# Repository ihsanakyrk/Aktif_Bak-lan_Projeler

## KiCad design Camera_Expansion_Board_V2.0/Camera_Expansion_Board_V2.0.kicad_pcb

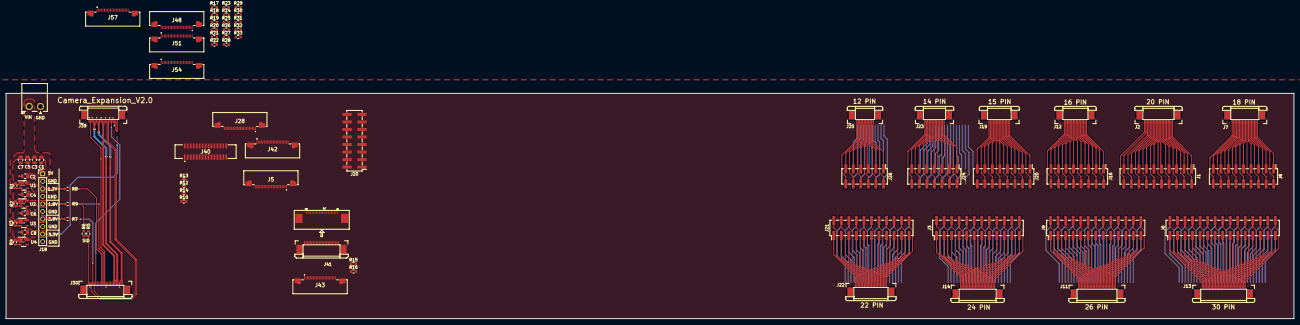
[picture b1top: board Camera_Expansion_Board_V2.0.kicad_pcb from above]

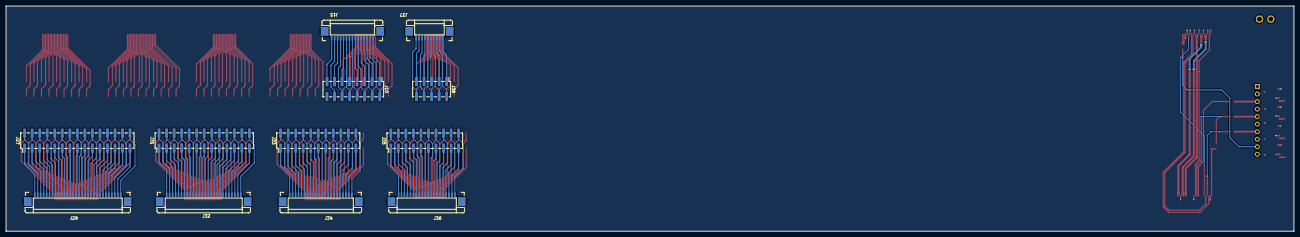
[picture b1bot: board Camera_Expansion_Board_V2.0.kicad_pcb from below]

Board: 2 copper layers, 434.4 x 76.0 mm, 92 parts (12 on the bottom side), 377 nets.

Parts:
C1, C2, C3, C4, C5, C6, C7, C8: 10uF; C_0805_2012Metric
J1, J35: PinHeader_2x10_P2.54mm_Vertical_MALE_SMD; PinHeader_2x10_P2.54mm_Vertical_SMD
J2, J39: FPC-05F-20PH20; FFC SOCKET DR_DWN 0.5MM -20P
J3: PinHeader_2x12_P2.54mm_Vertical_MALE_SMD; PinHeader_2x12_P2.54mm_Vertical_SMD
J4: 52435-2271
J5, J28, J42, J43, J48, J51, J54, J57: FFC SOCKET DR_BOTTOM 0.5MM -22P; F32R1A7H111022
J6, J27: PinHeader_2x15_P2.54mm_Vertical_MALE_SMD; PinHeader_2x15_P2.54mm_Vertical_SMD
J7: FPC-05F-18PH20; FFC SOCKET DR_DWN 0.5MM -18P
J8: PinHeader_2x9_P2.54mm_Vertical_MALE_SMD; PinHeader_2x09_P2.54mm_Vertical_SMD
J9, J31: PinHeader_2x13_P2.54mm_Vertical_MALE_SMD; PinHeader_2x13_P2.54mm_Vertical_SMD
J10: PinHeader_2x08_P2.54mm_Vertical_MALE_SMD; PinHeader_2x08_P2.54mm_Vertical_SMD
J11: FPC-05F-26PH20; FFC SOCKET DR_DWN 0.5MM-26P
J12: FPC-05F-16PH20; FFC SOCKET DR_DWN 0.5MM -16P
J13: FPC-05F-30PH20; FFC SOCKET DR_DWN 0.5MM-30P
J14, J30, J41: FPC-05F-24PH20; FFC SOCKET DR_DWN 0.5MM-24P
J15: AFA07-S15ECA-00
J16, J20, J20#2: PinHeader_2x8_P2.54mm_Vertical_MALE_SMD; PinHeader_2x08_P2.54mm_Vertical_SMD
J17: KF2EDGH-3.81-2P- Right Angle; KF2EDGH-3.81-2P
J18: PinHeader_1x10_P2.54mm_Vertical_MALE_TH; PinHeader_1x10_P2.54mm_Vertical
J19: FPC-05F-15PH20; FFC SOCKET DR_DWN 0.5MM -15P
J21, J33: PinHeader_2x11_P2.54mm_Vertical_MALE_SMD; PinHeader_2x11_P2.54mm_Vertical_SMD
J22: FPC-05F-22PH20; FFC SOCKET DR_DWN 0.5MM -22P
J23: FPC-05F-14PH20; FFC SOCKET DR_DWN 0.5MM -14P
J24: PinHeader_2x7_P2.54mm_Vertical_MALE_SMD; PinHeader_2x07_P2.54mm_Vertical_SMD
J25: FPC-05F-12PH20; FFC SOCKET DR_DWN 0.5MM -12P
J26: PinHeader_2x6_P2.54mm_Vertical_MALE_SMD; PinHeader_2x06_P2.54mm_Vertical_SMD
J29: AFA07-S30ECA-00
J32: AFA07-S26ECA-00
J34: AFA07-S22ECA-00
J36: AFA07-S20ECA-00
J37: AFA07-S10ECA-00
J38: PinHeader_2x5_P2.54mm_Vertical_MALE_SMD; PinHeader_2x05_P2.54mm_Vertical_SMD
J40: 117342485
R1, R2, R3, R4: 5K; R_0603_1608Metric
R5, R7, R8, R9, R15, R16, R17, R18, R19, R20, R21, R22, R23, R24, R25, R26, R27, R28, R29, R30, R31, R32, R33: 0R; R_0603_1608Metric
R6, R10: DNP; R_0603_1608Metric
R12, R13, R14: 0R; R_0402_1005Metric
U1: RT9080-12GJ5; SOT-23-5
U2: RT9080-18GJ5; SOT-23-5
U3: RT9080-28GJ5; SOT-23-5
U4: RT9080-33GJ5; SOT-23-5

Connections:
3V3: R12.1, R13.1, R14.1
/+3V3: J4.22, J39.19, J39.20, R10.2
/CSI2_CLK_N: J5.8, J28.15
/CSI2_CLK_P: J5.9, J28.14
/CSI2_D0_N: J5.2, J28.21
/CSI2_D0_P: J5.3, J28.20
/CSI2_D1_N: J5.5, J28.18
/CSI2_D1_P: J5.6, J28.17
/CSI_C_N: J42.15, J43.15, J48.15, J51.15, J54.15, J57.15
/CSI_C_P: J42.14, J43.14, J48.14, J51.14, J54.14, J57.14
/CSI_D0_N: J42.21, J43.21, J48.21, J51.21, J54.21, J57.21
/CSI_D0_P: J42.20, J43.20, J48.20, J51.20, J54.20, J57.20
/CSI_D1_N: J42.18, J43.18, J48.18, J51.18, J54.18, J57.18
/CSI_D1_P: J42.17, J43.17, J48.17, J51.17, J54.17, J57.17
/CSI_D2_N: J42.12, J43.12, J48.12, J51.12, J54.12, J57.12
/CSI_D2_P: J42.11, J43.11, J48.11, J51.11, J54.11, J57.11
/CSI_D3_N: J42.9, J43.9, J48.9, J51.9, J54.9, J57.9
/CSI_D3_P: J42.8, J43.8, J48.8, J51.8, J54.8, J57.8
/EXT_XVCLK: J5.17, J28.6, J42.6, J43.6, J48.6, J51.6, J54.6, J57.6
/FSIN: J5.18, J28.5, J42.5, J43.5, J48.5, J51.5, J54.5, J57.5
/I2C_SCL: J42.3, J43.3, J48.3, J51.3, J54.3, J57.3
/I2C_SDA: J42.2, J43.2, J48.2, J51.2, J54.2, J57.2
/MCLK: J30.12, J39.2
/MCN: J30.24, J39.8
/MCP: J30.23, J39.7
/MDN0: J30.21, J39.5
/MDN1: J30.19, J39.11
/MDP0: J30.20, J39.4
/MDP1: J30.18, J39.10
/MIPI_I2C_SCL: J5.20, J28.3, J30.5, J39.13
/MIPI_I2C_SDA: J5.21, J28.2, J30.3, J39.14
/MIPI_LVDS_RST: J30.6, J39.16
/SID: J30.1, R5.2, R6.1
AVDD: J30.4, R7.1
DGND: J5.1, J5.4, J5.7, J5.10, J5.13, J5.16, J5.19, J28.4, J28.7, J28.10, J28.13, J28.16, J28.19, J28.22
DOVDD: J30.11, R6.2, R9.1
DVDD: J30.10, R8.1
GND: C1.2, C2.2, C3.2, C4.2, C5.2, C6.2, C7.2, C8.2, J2.21, J2.22, J4.1, J4.4, J4.7, J4.10, J4.13, J4.16, J4.19, J5.23, J5.24, J7.19, J7.20, J11.27, J11.28, J12.17, J12.18, J13.31 (Pin_29), J13.32 (Pin_30), J14.25 (Pin_23), J14.26 (Pin_24), J15.16 (Pin_14), J15.17 (Pin_15), J17.1, J18.2, J18.4, J18.6, J18.8, J18.10, J19.16, J19.17, J22.23, J22.24, J23.15, J23.16, J25.13, J25.14, J28.23, J28.24, J29.31 (Pin_29), J29.32 (Pin_30), J30.2, J30.13, J30.22, J30.25 (Pin_23), J30.26 (Pin_24), J32.27, J32.28, J34.23, J34.24, J36.21, J36.22, J37.11, J37.12, J39.1, J39.3, J39.6, J39.9, J39.12, J39.15, J39.17, J39.18, J39.21, J39.22, J40.1, J40.7, J40.13, J40.19, J41.1, J41.2, J41.11, J42.4, J42.7, J42.10, J42.13, J42.16, J42.19, J42.22, J42.23, J42.24, J43.4, J43.7, J43.10, J43.13, J43.16, J43.19, J43.22, J43.23, J43.24, J48.4, J48.7, J48.10, J48.13, J48.16, J48.19, J48.22, J48.23, J48.24, J51.4, J51.7, J51.10, J51.13, J51.16, J51.19, J51.22, J51.23, J51.24, J54.4, J54.7, J54.10, J54.13, J54.16, J54.19, J54.22, J54.23, J54.24, J57.4, J57.7, J57.10, J57.13, J57.16, J57.19, J57.22, J57.23, J57.24, R5.1, U1.2 (GND), U2.2 (GND), U3.2 (GND), U4.2 (GND)
unnamed: J1.1, J2.1
unnamed: J1.2, J2.2
unnamed: J1.3, J2.3
unnamed: J1.4, J2.4
unnamed: J1.5, J2.5
unnamed: J1.6, J2.6
unnamed: J1.7, J2.7
unnamed: J1.8, J2.8
unnamed: J1.9, J2.9
unnamed: J1.10, J2.10
unnamed: J1.11, J2.11
unnamed: J1.12, J2.12
unnamed: J1.13, J2.13
unnamed: J1.14, J2.14
unnamed: J1.15, J2.15
unnamed: J1.16, J2.16
unnamed: J1.17, J2.17
unnamed: J1.18, J2.18
unnamed: J1.19, J2.19
unnamed: J1.20, J2.20
unnamed: J3.23, J14.23
unnamed: J3.24, J14.24
unnamed: J5.22, R12.2
unnamed: J6.29, J13.29
unnamed: J6.30, J13.30
unnamed: J7.1, J8.1
unnamed: J7.2, J8.2
unnamed: J7.3, J8.3
unnamed: J7.4, J8.4
unnamed: J7.5, J8.5
unnamed: J7.6, J8.6
unnamed: J7.7, J8.7
unnamed: J7.8, J8.8
unnamed: J7.9, J8.9
unnamed: J7.10, J8.10
unnamed: J7.11, J8.11
unnamed: J7.12, J8.12
unnamed: J7.13, J8.13
unnamed: J7.14, J8.14
unnamed: J7.15, J8.15
unnamed: J7.16, J8.16
unnamed: J7.17, J8.17
unnamed: J7.18, J8.18
unnamed: J10.1, J15.1
unnamed: J10.2, J15.2
unnamed: J10.3, J15.3
unnamed: J10.4, J15.4
unnamed: J10.5, J15.5
unnamed: J10.6, J15.6
unnamed: J10.7, J15.7
unnamed: J10.8, J15.8
unnamed: J10.9, J15.9
unnamed: J10.10, J15.10
unnamed: J10.11, J15.11
unnamed: J10.12, J15.12
unnamed: J10.13, J15.13
unnamed: J10.14, J15.14
unnamed: J10.15, J15.15
unnamed: J9.1, J11.1
unnamed: J9.2, J11.2
unnamed: J9.3, J11.3
unnamed: J9.4, J11.4
unnamed: J9.5, J11.5
unnamed: J9.6, J11.6
unnamed: J9.7, J11.7
unnamed: J9.8, J11.8
unnamed: J9.9, J11.9
unnamed: J9.10, J11.10
unnamed: J9.11, J11.11
unnamed: J9.12, J11.12
unnamed: J9.13, J11.13
unnamed: J9.14, J11.14
unnamed: J9.15, J11.15
unnamed: J9.16, J11.16
unnamed: J9.17, J11.17
unnamed: J9.18, J11.18
unnamed: J9.19, J11.19
unnamed: J9.20, J11.20
unnamed: J9.21, J11.21
unnamed: J9.22, J11.22
unnamed: J9.23, J11.23
unnamed: J9.24, J11.24
unnamed: J9.25, J11.25
unnamed: J9.26, J11.26
unnamed: J12.1, J16.1
unnamed: J12.2, J16.2
unnamed: J12.3, J16.3
unnamed: J12.4, J16.4
unnamed: J12.5, J16.5
unnamed: J12.6, J16.6
unnamed: J12.7, J16.7
unnamed: J12.8, J16.8
unnamed: J12.9, J16.9
unnamed: J12.10, J16.10
unnamed: J12.11, J16.11
unnamed: J12.12, J16.12
unnamed: J12.13, J16.13
unnamed: J12.14, J16.14
unnamed: J12.15, J16.15
unnamed: J12.16, J16.16
unnamed: J6.1, J13.1
unnamed: J6.2, J13.2
unnamed: J6.3, J13.3
unnamed: J6.4, J13.4
unnamed: J6.5, J13.5
unnamed: J6.6, J13.6
unnamed: J6.7, J13.7
unnamed: J6.8, J13.8
unnamed: J6.9, J13.9
unnamed: J6.10, J13.10
unnamed: J6.11, J13.11
unnamed: J6.12, J13.12
unnamed: J6.13, J13.13
unnamed: J6.14, J13.14
unnamed: J6.15, J13.15
unnamed: J6.16, J13.16
unnamed: J6.17, J13.17
unnamed: J6.18, J13.18
unnamed: J6.19, J13.19
unnamed: J6.20, J13.20
unnamed: J6.21, J13.21
unnamed: J6.22, J13.22
unnamed: J6.23, J13.23
unnamed: J6.24, J13.24
unnamed: J6.25, J13.25
unnamed: J6.26, J13.26
unnamed: J6.27, J13.27
unnamed: J6.28, J13.28
unnamed: J3.1, J14.1
unnamed: J3.2, J14.2
unnamed: J3.3, J14.3
unnamed: J3.4, J14.4
unnamed: J3.5, J14.5
unnamed: J3.6, J14.6
unnamed: J3.7, J14.7
unnamed: J3.8, J14.8
unnamed: J3.9, J14.9
unnamed: J3.10, J14.10
unnamed: J3.11, J14.11
unnamed: J3.12, J14.12
unnamed: J3.13, J14.13
unnamed: J3.14, J14.14
unnamed: J3.15, J14.15
unnamed: J3.16, J14.16
unnamed: J3.17, J14.17
unnamed: J3.18, J14.18
unnamed: J3.19, J14.19
unnamed: J3.20, J14.20
unnamed: J3.21, J14.21
unnamed: J3.22, J14.22
unnamed: J19.1, J20.1, J20#2.1
unnamed: J19.2, J20.2, J20#2.2
unnamed: J19.3, J20.3, J20#2.3
unnamed: J19.4, J20.4, J20#2.4
unnamed: J19.5, J20.5, J20#2.5
unnamed: J19.6, J20.6, J20#2.6
unnamed: J19.7, J20.7, J20#2.7
unnamed: J19.8, J20.8, J20#2.8
unnamed: J19.9, J20.9, J20#2.9
unnamed: J19.10, J20.10, J20#2.10
unnamed: J19.11, J20.11, J20#2.11
unnamed: J19.12, J20.12, J20#2.12
unnamed: J19.13, J20.13, J20#2.13
unnamed: J19.14, J20.14, J20#2.14
unnamed: J19.15, J20.15, J20#2.15
unnamed: J21.1, J22.1
unnamed: J21.2, J22.2
unnamed: J21.3, J22.3
unnamed: J21.4, J22.4
unnamed: J21.5, J22.5
unnamed: J21.6, J22.6
unnamed: J21.7, J22.7
unnamed: J21.8, J22.8
unnamed: J21.9, J22.9
unnamed: J21.10, J22.10
unnamed: J21.11, J22.11
unnamed: J21.12, J22.12
unnamed: J21.13, J22.13
unnamed: J21.14, J22.14
unnamed: J21.15, J22.15
unnamed: J21.16, J22.16
unnamed: J21.17, J22.17
unnamed: J21.18, J22.18
unnamed: J21.19, J22.19
unnamed: J21.20, J22.20
unnamed: J21.21, J22.21
unnamed: J21.22, J22.22
unnamed: J23.1, J24.1
unnamed: J23.2, J24.2
unnamed: J23.3, J24.3
unnamed: J23.4, J24.4
unnamed: J23.5, J24.5
unnamed: J23.6, J24.6
unnamed: J23.7, J24.7
unnamed: J23.8, J24.8
unnamed: J23.9, J24.9
unnamed: J23.10, J24.10
unnamed: J23.11, J24.11
unnamed: J23.12, J24.12
unnamed: J23.13, J24.13
unnamed: J23.14, J24.14
unnamed: J25.1, J26.1
unnamed: J25.2, J26.2
unnamed: J25.3, J26.3
unnamed: J25.4, J26.4
unnamed: J25.5, J26.5
unnamed: J25.6, J26.6
unnamed: J25.7, J26.7
unnamed: J25.8, J26.8
unnamed: J25.9, J26.9
unnamed: J25.10, J26.10
unnamed: J25.11, J26.11
unnamed: J25.12, J26.12
unnamed: J27.1, J29.1
unnamed: J27.2, J29.2
unnamed: J27.3, J29.3
unnamed: J27.4, J29.4
unnamed: J27.5, J29.5
unnamed: J27.6, J29.6
unnamed: J27.7, J29.7
unnamed: J27.8, J29.8
unnamed: J27.9, J29.9
unnamed: J27.10, J29.10
unnamed: J27.11, J29.11
unnamed: J27.12, J29.12
unnamed: J27.13, J29.13
unnamed: J27.14, J29.14
unnamed: J27.15, J29.15
unnamed: J27.16, J29.16
unnamed: J27.17, J29.17
unnamed: J27.18, J29.18
unnamed: J27.19, J29.19
unnamed: J27.20, J29.20
unnamed: J27.21, J29.21
unnamed: J27.22, J29.22
unnamed: J27.23, J29.23
unnamed: J27.24, J29.24
unnamed: J27.25, J29.25
unnamed: J27.26, J29.26
unnamed: J27.27, J29.27
unnamed: J27.28, J29.28
unnamed: J27.29, J29.29
unnamed: J27.30, J29.30
unnamed: J28.1, R13.2
unnamed: J31.1, J32.1
unnamed: J31.2, J32.2
unnamed: J31.3, J32.3
unnamed: J31.4, J32.4
unnamed: J31.5, J32.5
unnamed: J31.6, J32.6
unnamed: J31.7, J32.7
unnamed: J31.8, J32.8
unnamed: J31.9, J32.9
unnamed: J31.10, J32.10
unnamed: J31.11, J32.11
unnamed: J31.12, J32.12
unnamed: J31.13, J32.13
unnamed: J31.14, J32.14
unnamed: J31.15, J32.15
unnamed: J31.16, J32.16
unnamed: J31.17, J32.17
unnamed: J31.18, J32.18
unnamed: J31.19, J32.19
unnamed: J31.20, J32.20
unnamed: J31.21, J32.21
unnamed: J31.22, J32.22
unnamed: J31.23, J32.23
unnamed: J31.24, J32.24
unnamed: J31.25, J32.25
unnamed: J31.26, J32.26
unnamed: J33.1, J34.1
unnamed: J33.2, J34.2
unnamed: J33.3, J34.3
unnamed: J33.4, J34.4
unnamed: J33.5, J34.5
unnamed: J33.6, J34.6
unnamed: J33.7, J34.7
unnamed: J33.8, J34.8
unnamed: J33.9, J34.9
unnamed: J33.10, J34.10
unnamed: J33.11, J34.11
unnamed: J33.12, J34.12
unnamed: J33.13, J34.13
unnamed: J33.14, J34.14
unnamed: J33.15, J34.15
unnamed: J33.16, J34.16
unnamed: J33.17, J34.17
unnamed: J33.18, J34.18
unnamed: J33.19, J34.19
unnamed: J33.20, J34.20
unnamed: J33.21, J34.21
unnamed: J33.22, J34.22
unnamed: J35.1, J36.1
unnamed: J35.2, J36.2
unnamed: J35.3, J36.3
unnamed: J35.4, J36.4
unnamed: J35.5, J36.5
unnamed: J35.6, J36.6
unnamed: J35.7, J36.7
unnamed: J35.8, J36.8
unnamed: J35.9, J36.9
unnamed: J35.10, J36.10
unnamed: J35.11, J36.11
unnamed: J35.12, J36.12
unnamed: J35.13, J36.13
unnamed: J35.14, J36.14
unnamed: J35.15, J36.15
unnamed: J35.16, J36.16
unnamed: J35.17, J36.17
unnamed: J35.18, J36.18
unnamed: J35.19, J36.19
unnamed: J35.20, J36.20
unnamed: J37.1, J38.1
unnamed: J37.2, J38.2
unnamed: J37.3, J38.3
unnamed: J37.4, J38.4
unnamed: J37.5, J38.5
unnamed: J37.6, J38.6
unnamed: J37.7, J38.7
unnamed: J37.8, J38.8
unnamed: J37.9, J38.9
unnamed: J37.10, J38.10
unnamed: J42.1, R15.2
unnamed: J43.1, R16.2
unnamed: J48.1, R21.2
unnamed: J51.1, R24.2
unnamed: J54.1, R27.2
unnamed: J57.1, R30.2
unnamed: R1.2, U1.3 (EN)
unnamed: R2.2, U2.3 (EN)
unnamed: R3.2, U3.3 (EN)
unnamed: R4.2, U4.3 (EN)
VCC: R17.1, R18.1, R19.1, R20.1, R22.1, R23.1, R25.1, R26.1, R28.1, R29.1, R31.1, R32.1
VCC_3V3: C8.1, J18.9, R10.1, U4.5 (OUT)
VDD_3V3: R15.1, R16.1, R21.1, R24.1, R27.1, R30.1, R33.1
VIN: C1.1, C3.1, C5.1, C7.1, J17.2, J18.1, R1.1, R2.1, R3.1, R4.1, U1.1 (IN), U2.1 (IN), U3.1 (IN), U4.1 (IN)
VOUT_1.2: C2.1, J18.3, R8.2, U1.5 (OUT)
VOUT_1.8: C4.1, J18.5, R9.2, U2.5 (OUT)
VOUT_2.8: C6.1, J18.7, R7.2, U3.5 (OUT)

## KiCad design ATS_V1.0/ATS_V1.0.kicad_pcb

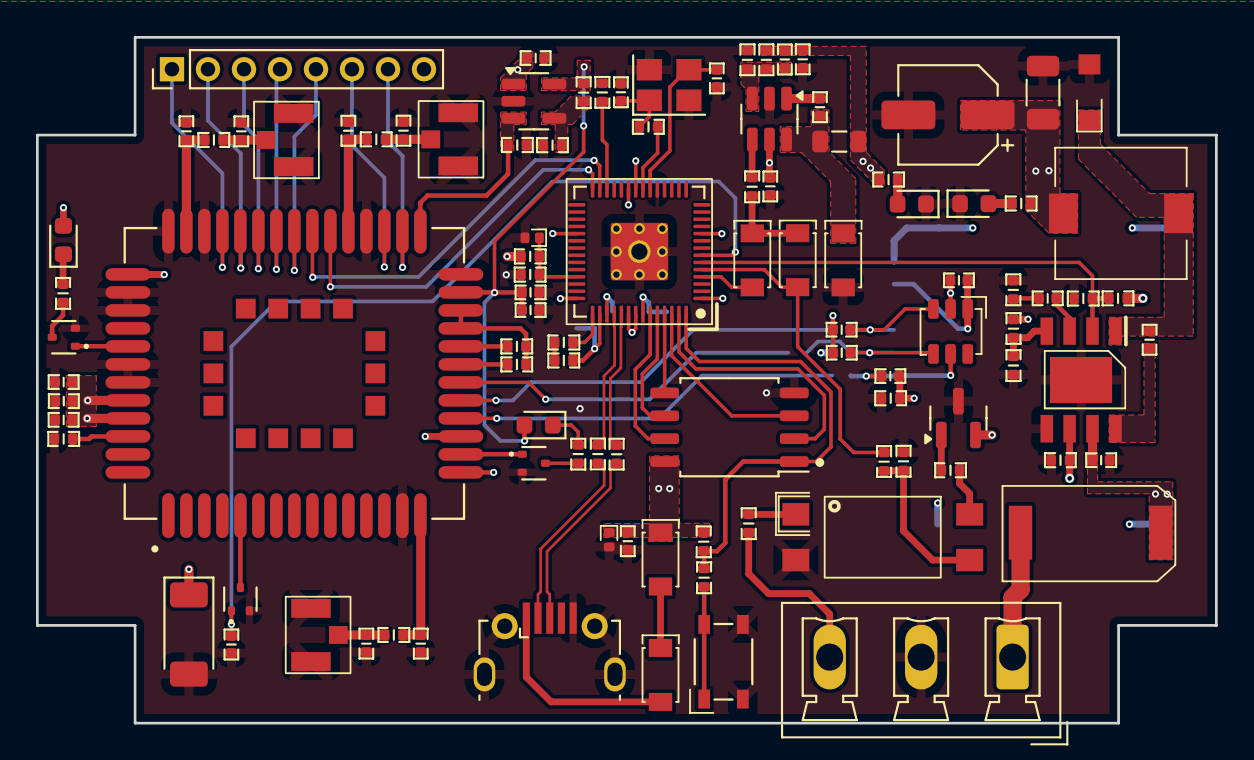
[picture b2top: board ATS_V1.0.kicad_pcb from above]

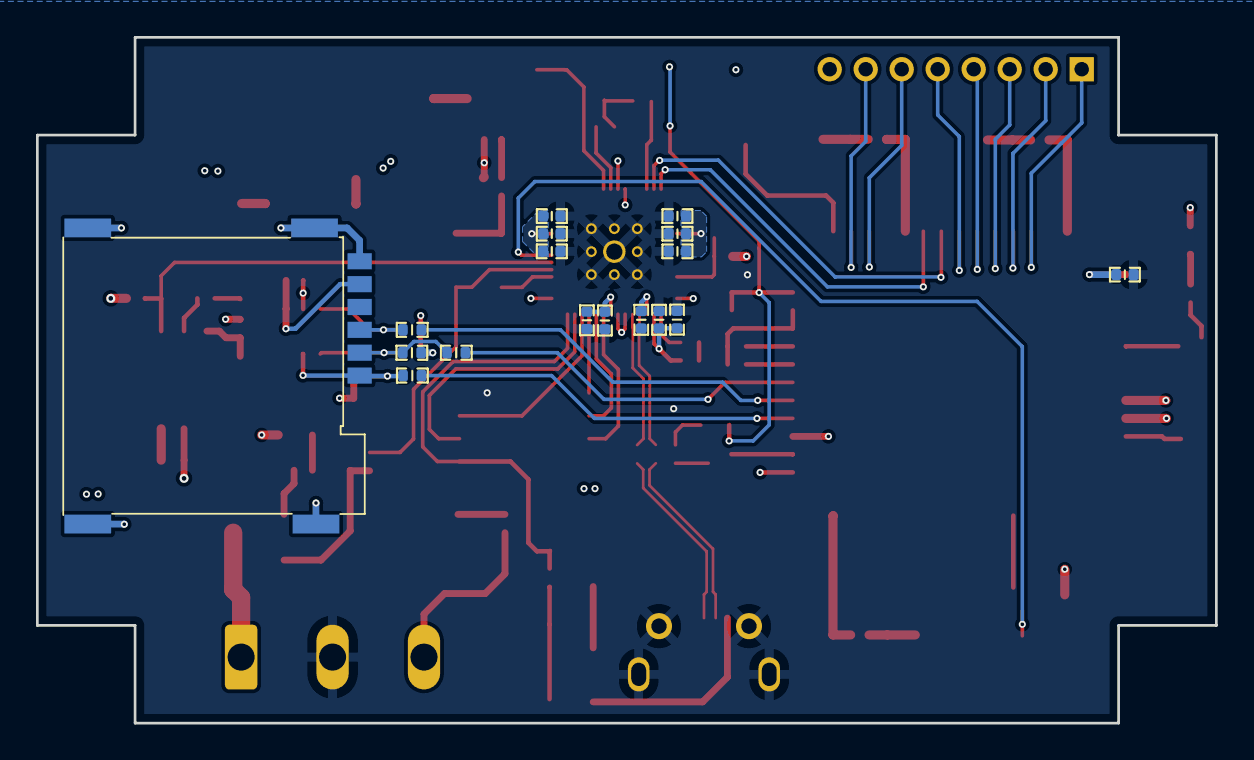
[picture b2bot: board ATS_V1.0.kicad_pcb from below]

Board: 4 copper layers, 65.5 x 38.1 mm, 119 parts (17 on the bottom side), 86 nets.

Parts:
C1, C46: 4.7uF; C_0402_1005Metric
C2, C3, C4, C5, C6, C7: 10pF_DNP; C_0402_1005Metric
C8, C9, C10, C11, C33, C45, C80: 33pF; C_0402_1005Metric
C12, C81: 10uF; C_0402_1005Metric
C13, C18, C19, C22, C23, C24, C25, C26, C31, C39, C40, C41, C42, C48: 100nF; C_0402_1005Metric
C14, C15: 27pF; C_0402_1005Metric
C20, C21: 1uF; C_0402_1005Metric
C30: 100uF; CP_Elec_5x5.7
C34, C35: 10pF; C_0402_1005Metric
C43: 150pF; C_0402_1005Metric
C44: 100uF; C_1206_3216Metric
C79: 4.7uF/50V; C_0402_1005Metric
CN4: HX MICRO SIM 6P H1.35
D2: LED_RED; LED_0603_1608Metric
D3: LED_GREEN; LED_0603_1608Metric
D5: SS34FA
D6, D18: LED_WHITE; LED_0603_1608Metric
D7: PDZVTR5.1B; D_SOD-128
D8: ESDA6V1-5SC6
D9: S6MC
D10, D16, D17, D19, D32: SS14
D11, D15: ESD5341N
H2: DNP; PinHeader_1x08_P2.00mm_Vertical
IC2: MP1584EN; MP1584N
IC5: BL9342; SOT-23-6
J4, J5, J6: IPEX1-3-TXZ 214
J9: KF2EDGR-Y-5.08-3P-Right Angle
J20: MICRO XNJ ZB; Micro-B SMD
L2: CDRH74NP-100MC-B; CDRH74NP100MCB
L7: LQM21PN2R2MC0D; L_0805_2012Metric
Q1, Q2, Q3: DTC114E; SOT-523
R2, R3, R4, R11, R12, R13: 0R; R_0402_1005Metric
R5, R26, R32: 100K; R_0402_1005Metric
R6, R7, R10: 22R; R_0402_1005Metric
R8: 390R; R_0402_1005Metric
R9: 270R; R_0402_1005Metric
R15: 200R; R_0402_1005Metric
R20: 47K; R_0402_1005Metric
R21: 1R; R_0402_1005Metric
R22, R23: 27R; R_0402_1005Metric
R24, R25, R44, R48: 1K; R_0402_1005Metric
R27: 2.2K; R_0402_1005Metric
R28: 75K %1; R_0402_1005Metric
R29: 43K %1; R_0402_1005Metric
R31: 200K; R_0402_1005Metric
R33, R40, R49: DNP; R_0402_1005Metric
R34, R45: 40.2K; R_0402_1005Metric
R36: 160K; R_0402_1005Metric
R37: 124K; R_0402_1005Metric
R38, R47: 4.7K; R_0402_1005Metric
R39: 3.3K; R_0402_1005Metric
R41: 33R; R_0402_1005Metric
R43, R50, R51: 10K; R_0402_1005Metric
S2: SKRPANE010
U1: MC60_0; XCVR_MC60
U4: SGM2019-ADJYN5G/TR; SOT-23-5
U5: RP2040; RP2040-QFN-56
U6: PC817C; PC817
U7: W25Q16JVSIQ
U8: TLV76033DBZT; SOT-23
Y1: CF4012M00020001; Crystal_SMD_3225-4Pin_3.2x2.5mm

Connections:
4V: C30.1 (+), C31.1 (+), C33.1 (+), C34.1 (+), C35.1 (+), C44.1, D2.2 (A), D7.1 (K), L2.2, R36.2, R38.1, U1.50 (VBAT), U1.51 (VBAT), U4.1 (VIN)
+1V1: C18.1, C19.1, C20.1, U5.23 (DVDD), U5.45 (VREG_VOUT), U5.50 (DVDD)
/1PPS: Q2.1 (B), U1.17 (1PPS)
/ANT_BT: C6.2 (-), R4.2, U1.32 (BT_ANT)
/ANT_GNSS: C4.2 (-), R3.2, U1.15 (GNSS_ANT)
/ANT_GPS: C2.2 (-), R2.2, U1.41 (RF_ANT)
/CTS>: H2.2, U1.38 (CTS)
/DBG_RXD: H2.6, U1.30 (DBG_RXD)
/DBG_TXD: H2.7, U1.29 (DBG_TXD)
/DCD>: H2.4, U1.36 (DCD)
/DTR>: H2.3, U1.37 (DTR/SIM1_PRESENCE)
/GNSS_VCC_EN: R20.1, U1.28 (GNSS_VCC_EN), U4.3 (EN)
/GPIO2: D16.A, U5.4 (GPIO2)
/GPIO3: D17.A, R44.2, U5.5 (GPIO3)
/GPIO4: IC2.2 (EN), R26.2, R27.1, U5.6 (GPIO4)
/GPIO5: C45.2 (-), Q3.1 (B), U5.7 (GPIO5)
/GPIO16: U1.34 (RXD), U5.27 (GPIO16)
/GPIO17: U1.33 (TXD), U5.28 (GPIO17)
/GPIO27_ADC1: D11.1, R48.1, R50.2, U5.39 (GPIO27_ADC1)
/Micro: D32.A, J20.1 (VBUS)
/NETLIGHT: Q1.1 (B), U1.47 (NETLIGHT)
/PWRKEY: Q3.3 (C), U1.5 (PWRKEY)
/QSPI_SCLK: U5.52 (QSPI_SCLK), U7.6 (CLK)
/QSPI_SD0: U5.53 (QSPI_SD0), U7.5 (DI(IO0))
/QSPI_SD1: U5.55 (QSPI_SD1), U7.2 (DO(IO1))
/QSPI_SD2: U5.54 (QSPI_SD2), U7.3 (IO2)
/QSPI_SD3: U5.51 (QSPI_SD3), U7.7 (IO3)
/QSPI_SS: R25.1, R33.2, U5.56 (QSPI_SS), U7.1 (~CS)
/RING>: H2.5, U1.35 (RI)
/RTS>: H2.1, U1.39 (RTS)
/RXD_AUX: R12.1, R13.1, U1.24 (RXD_AUX), U1.25 (TXD_AUX)
/RXD_G: R13.2, U1.23 (GNSS_RXD)
/SIM1_VDD: C11.2 (-), CN4.C1 (VCC), D8.1, R5.1, U1.18 (SIM1_VDD)
/SIMCLK: C9.2 (-), CN4.C3 (CLK), D8.5, R7.1
/SIMDAT: C8.2 (-), CN4.C7 (I/O), D8.4, R5.2, R10.1
/SIMRST: C10.2 (-), CN4.C2 (RST), D8.3, R6.1
/SIM_CLK: R7.2, U1.19 (SIM1_CLK)
/SIM_DAT: R10.2, U1.21 (SIM1_DATA)
/SIM_RST: R6.2, U1.20 (SIM1_RST)
/TXD_G: R12.2, U1.22 (GNSS_TXD)
/USB_D+: J20.3 (DP), R22.1
/USB_D-: J20.2 (DM), R23.1
/USB_D_N: R23.2, U5.46 (USB_DM)
/USB_D_P: R22.2, U5.47 (USB_DP)
/VDD_EXT: C1.1 (+), U1.43 (VDD_EXT)
/VRTC: R40.2, U1.52 (VRTC)
/XIN: C14.1, U5.20 (XIN), Y1.3
/XOUT: R24.1, U5.21 (XOUT)
/~USB_BOOT: R25.2, S2.1, S2.2
ADC_VREF: R15.2, R21.1
Earth: C1.2 (-), C2.1 (+), C3.1 (+), C4.1 (+), C5.1 (+), C6.1 (+), C7.1 (+), C12.1, C14.2, C15.2, C18.2, C19.2, C20.2, C21.2, C22.2, C23.2, C24.2, C25.2, C26.2, C30.2 (-), C31.2 (-), C33.2 (-), C34.2 (-), C35.2 (-), C39.2 (-), C40.2, C41.2, C42.2, C44.2, C45.1 (+), C46.2 (-), C79.1, C81.1, D5.2, D6.1 (K), D7.2 (A), D10.A, D11.2, D15.2, D18.1 (K), IC2.5 (GND), IC2.9 (EP), IC5.2 (GND), J4.2, J4.3, J5.2, J5.3, J6.2, J6.3, J9.2, J20.5 (GND), J20.6 (Shield), Q1.2 (E), Q2.2 (E), Q3.2 (E), R11.2, R20.2, R27.2, R29.2, R31.2, R32.2, R34.2, R40.1, R43.2, R45.2, R48.2, S2.3, S2.4, U1.14 (GND), U1.27 (GND), U1.31 (GND), U1.40 (GND), U1.42 (GND), U1.44 (GND), U1.45 (GND), U1.48 (GND), U1.49 (GND), U4.2 (GND), U5.19 (TESTEN), U5.57 (GND), U6.2 (K), U7.4 (GND), U8.3 (GND), Y1.2, Y1.4
GNDD: C8.1 (+), C9.1 (+), C10.1 (+), C11.1 (+), CN4.C5 (GND), CN4.GND, D8.2, R11.1, U1.16 (SIM_GND)
GNSSVCC: C39.1 (+), C46.1 (+), D3.2 (A), R28.1, U1.26 (GNSS_VCC), U4.5 (VOUT)
IGN: J9.3, R39.2
IGN_V: R41.1, U8.1 (OUT)
unnamed: C3.2 (-), J4.1, R2.1
unnamed: C5.2 (-), J5.1, R3.1
unnamed: C7.2 (-), J6.1, R4.1
unnamed: C15.1, R24.2, Y1.1
unnamed: C43.1, R32.1
unnamed: D2.1 (K), R8.1
unnamed: D3.1 (K), R9.1
unnamed: D6.2 (A), R38.2
unnamed: D16.C, D17.C, R51.2
unnamed: D18.2 (A), R47.2
unnamed: D19.A, D32.C
unnamed: C13.2, IC2.8 (BST)
unnamed: C43.2, IC2.3 (COMP)
unnamed: IC2.4 (FB), R34.1, R36.1
unnamed: IC2.6 (FREQ), R31.1
unnamed: C13.1, D5.1, IC2.1 (SW), L2.1
unnamed: C48.1, IC5.1 (BS)
unnamed: IC5.4 (EN), R51.1
unnamed: C80.2, IC5.3 (FB), R37.1, R45.1
unnamed: C48.2, D10.C, IC5.6 (SW), L7.2
unnamed: Q1.3 (C), R8.2
unnamed: Q2.3 (C), R9.2
unnamed: R28.2, R29.1, U4.4 (FB)
unnamed: R21.2, U5.43 (ADC_AVDD)
unnamed: R49.1, U5.26 (RUN)
unnamed: R39.1, U6.1 (A)
unnamed: R41.2, U6.4 (C)
unnamed: R43.1, R44.1, U6.3 (E)
RP2040_3V3: C21.1, C22.1, C23.1, C24.1, C25.1, C26.1, C40.1, C41.1, C42.1, C80.1, C81.2, D15.1, D19.C, L7.1, R15.1, R33.1, R37.2, R47.1, U5.1 (IOVDD), U5.10 (IOVDD), U5.22 (IOVDD), U5.33 (IOVDD), U5.42 (IOVDD), U5.44 (VREG_IN), U5.48 (USB_VDD), U5.49 (IOVDD), U7.8 (VCC)
VIN: C12.2, C79.2, D9.1, IC2.7 (VIN), IC5.5 (IN), R26.1, R50.1, U8.2 (IN)
VRAW: D9.2, J9.1
